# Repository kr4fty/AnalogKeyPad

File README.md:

Fork of the library made by oryshed (oryshed dot gmail dot com)

**Original**: [http://www.oryshed.com/arduino/lcd-48x84-shield] (http://www.oryshed.com/arduino/lcd-48x84-shield)

Library that gives us the possibility to use up to 5 buttons connected to a single analog port.

## Hardware

<p align="center">
  <br><br>
  <b>Circuito</b><br>
  
  <br><br>
  <b>Vista 3D</b><br>
  
</p>

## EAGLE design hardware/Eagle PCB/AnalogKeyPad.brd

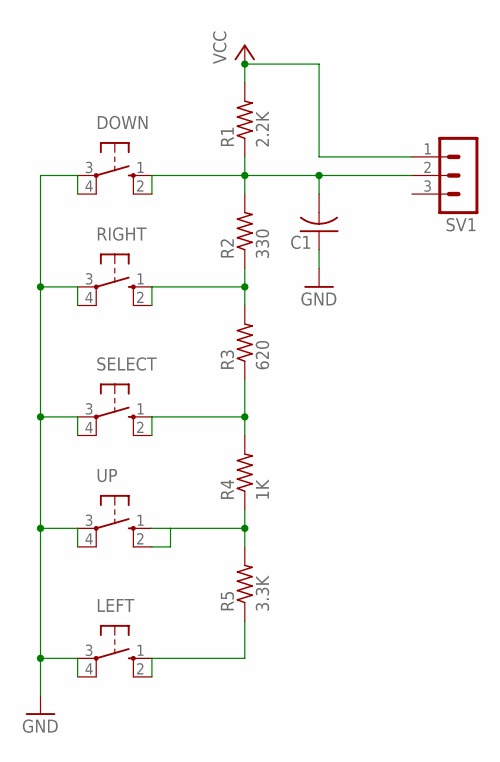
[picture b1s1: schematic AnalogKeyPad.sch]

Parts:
C1: C-US050-024X044; C050-024X044
DOWN: 10-XX; B3F-10XX
LEFT: 10-XX; B3F-10XX
R1: 2.2K; 0207/7
R2: 330; 0207/7
R3: 620; 0207/7
R4: 1K; 0207/7
R5: 3.3K; 0207/7
RIGHT: 10-XX; B3F-10XX
SELECT: 10-XX; B3F-10XX
SV1: MA03-1
UP: 10-XX; B3F-10XX

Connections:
A0: C1.2, DOWN.1 (S), DOWN.2 (S1), R1.1, R2.2, SV1.2
GND: C1.1, DOWN.3, DOWN.4 (P1), LEFT.3, LEFT.4 (P1), RIGHT.3, RIGHT.4 (P1), SELECT.3, SELECT.4 (P1), UP.3, UP.4 (P1)
unnamed: R2.1, R3.2, RIGHT.1 (S), RIGHT.2 (S1)
unnamed: LEFT.1 (S), LEFT.2 (S1), R5.1
unnamed: R3.1, R4.2, SELECT.1 (S), SELECT.2 (S1)
unnamed: R4.1, R5.2, UP.1 (S), UP.2 (S1)
VCC: R1.2, SV1.1

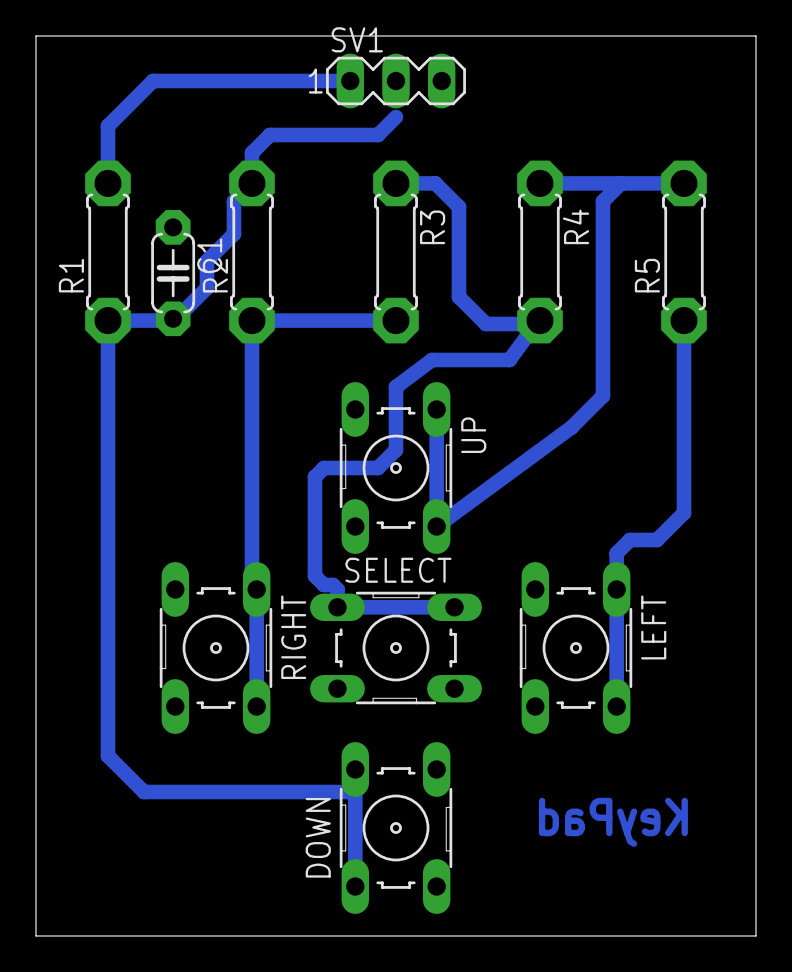
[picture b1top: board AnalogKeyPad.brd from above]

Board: 2 copper layers, 40.0 x 50.0 mm, 12 parts (0 on the bottom side), 7 nets.

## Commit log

2017-03-02 hardware
2017-06-01 update schematic
2017-06-01 add .gitattributes
2017-07-10 update hardware
